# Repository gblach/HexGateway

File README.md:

# HexGateway
An internet gateway for Bluetooth LE, OpenThread and/or Zigbee devices.

It employs three chips:
- nrf52840 - has support for Bluetooth LE, OpenThread and Zigbee networks.
- esp32-c3 - has support for WiFi at 2.4GHz.
- enc28j60 - has support for Ethernet network.

## Hardware
To build your own board you need this [gerber file](HexGateway.zip) and [bill of materials](HexGateway.csv).

Note that U102 is required only if your are using esp32-c3 (U101) without built-in flash memory.

## Programmers
nrf52840 (U1) can be programmed using the standalone [Segger J-Link](https://www.segger.com/products/debug-probes/j-link/) or the on-board Segger J-Link (this can be found for e.g. on [nrf52840dk](https://www.nordicsemi.com/Products/Development-hardware/nRF52840-DK) board). This programmer must be connected to J1 (TagConnect) or J2 (IDC 10) connector.

esp32-c3 (U101) can be programmed using [ESP-Prog](https://docs.espressif.com/projects/espressif-esp-iot-solution/en/latest/hw-reference/ESP-Prog_guide.html). This programmer must be connected to J101 (TagConnect) or J102 (IDC 6) connector.

enc28j60 (U201) does not need to be programmed.

## Software
For the nrf52840 chip you have to write your own software that will meet your requirements. The best way is to use [Zephyr RTOS](https://www.zephyrproject.org/). The board definition for Zephyr can be found in [boards/arm/hexgw1](boards/arm/hexgw1) directory.

esp32-c3 can be controlled with AT commands. To do this, you need to upload [ESP-AT](https://github.com/espressif/esp-at) firmware.

## Sponsorship

The production of these gateways was sponsored by [PCBWay](https://pcbway.com/g/7D2Z6d), they manufacture prototype PCBs and assemble components on the boards. I got 5 almost complete devices from this company for testing and evaluation, I had to solder only connectors for antennas and RJ45 ports by myself.

The visual impression of the boards is very good. All the contacts are gold plated, the silkscreen is readable, the whole board is thoroughly covered with soldiermask and all the components are soldered with a small amount of tin, so I was not worried about a potential short circuit anywhere.

So it remained to upload test programs to check if everything works properly. First I uploaded ESP-AT to the ESP32-C3 chips, and that passed without any problem. Next, I uploaded four programs one at a time to the nRF52840 chips. The first to check if bluetooth works, the second to check WiFi operation, the third to check Ethernet and the fourth to check LEDs. In the case of 4/5 boards, everything works as expected, so they are fully functional devices. However, for the fifth one, the programmer gave me a message that it does not detect the voltage of the processor. With a multimeter I checked the voltage on the VDD pin and there was indeed 0V there. This means that this chip is defective or more likely not all pins are soldered correctly. I am not surprised by this situation, because the nrf52840 chip has very small and densely spaced pins, so if something was to be soldered wrong, it would be with this chip.

My final rating for the quality of devices produced by [PCBWay](https://pcbway.com/g/7D2Z6d) is 4/5 stars, and this is higher than the two competing companies I have worked with. So I will probably change the company where I will produce the PCBs in the future.

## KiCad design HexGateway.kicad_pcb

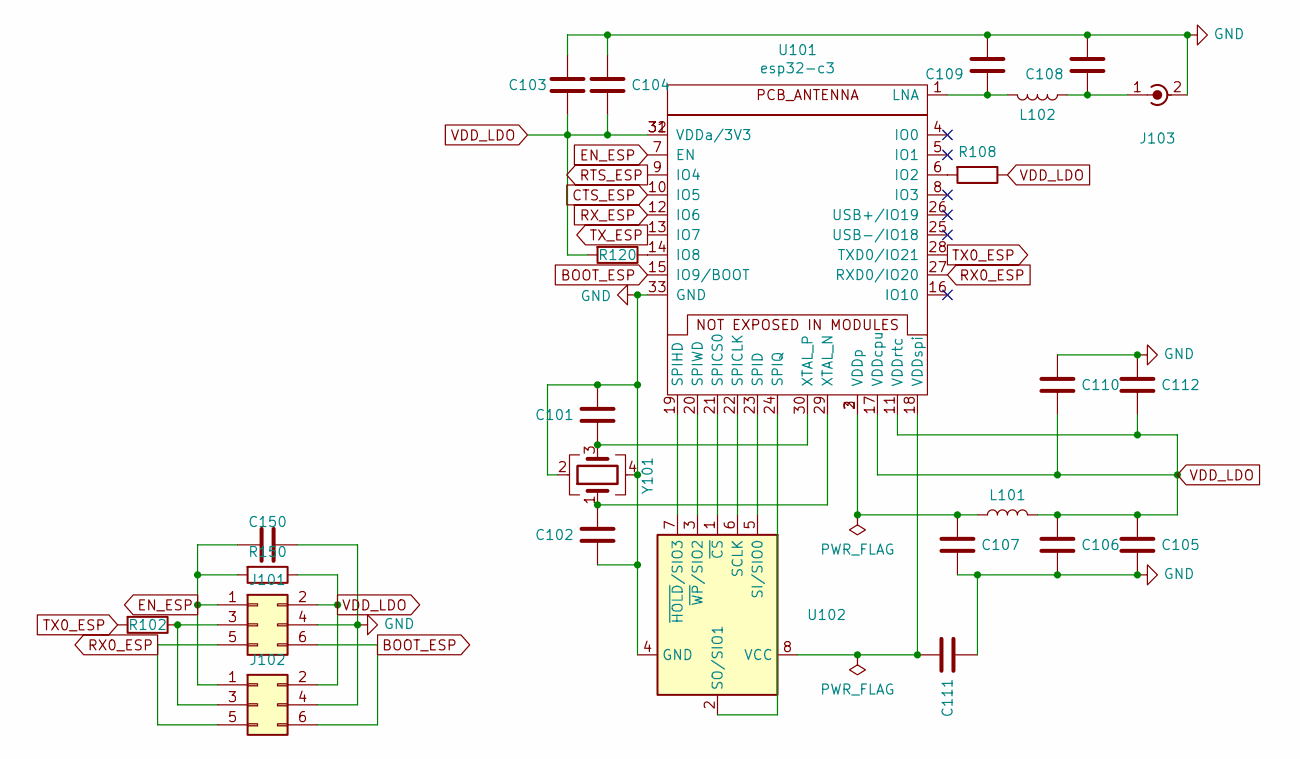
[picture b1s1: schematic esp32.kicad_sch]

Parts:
C101, C102: 20pF; C_0402_1005Metric_Pad0.74x0.62mm_HandSolder; LCSC C1554
C103, C150: 1uF, 20%; C_0402_1005Metric_Pad0.74x0.62mm_HandSolder; LCSC C52923
C104: 10nF, 10%; C_0402_1005Metric_Pad0.74x0.62mm_HandSolder; LCSC C15195
C105: 10uF, 20%; C_0402_1005Metric_Pad0.74x0.62mm_HandSolder; LCSC C15525
C106, C107, C110, C112: 100nF, X7R, 10%; C_0402_1005Metric_Pad0.74x0.62mm_HandSolder; LCSC C1525
C108: 2.0pF; C_0402_1005Metric_Pad0.74x0.62mm_HandSolder; LCSC C1558
C109: 1.5pF; C_0402_1005Metric_Pad0.74x0.62mm_HandSolder; LCSC C23967
C111: 1uF, 20%; C_0402_1005Metric_Pad0.74x0.62mm_HandSolder; LCSC C29266
J101: Conn_02x03_Odd_Even; Tag-Connect_TC2030-IDC-NL_2x03_P1.27mm_Vertical
J102: Conn_02x03_Odd_Even; PinHeader_2x03_P1.27mm_Vertical
J103: Conn_Coaxial; SMA_EdgeMount
L101: 2.0nH, (0.1nH), 450mA; L_0402_1005Metric_Pad0.77x0.64mm_HandSolder; LCSC C87176
L102: 3.9nH; L_0402_1005Metric_Pad0.77x0.64mm_HandSolder; LCSC C14033
R102: 499R, 1%, 1/20W; R_0402_1005Metric_Pad0.72x0.64mm_HandSolder; LCSC C57982
R108, R120, R150: 10k, 1%; R_0402_1005Metric_Pad0.72x0.64mm_HandSolder; LCSC C25744
U101: esp32-c3; QFN-32-1EP_5x5mm_P0.5mm_EP3.7x3.7mm; LCSC C2838500
U102: MX25R3235FM2xx1; SOP-8_5.28x5.23mm_P1.27mm; LCSC C18192
Y101: 40MHz, 15pF, 10ppm; Crystal_SMD_3225-4Pin_3.2x2.5mm; LCSC C90935

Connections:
BOOT_ESP: J101.6, J102.6, U101.15 (IO9/BOOT)
CTS_ESP: U101.10 (IO5); also elsewhere on the board
EN_ESP: C150.1, J101.1, J102.1, R150.2, U101.7 (EN)
GND: C101.2, C102.2, C103.1, C104.1, C105.2, C106.2, C107.2, C108.2, C109.2, C110.1, C111.1, C112.1, C150.2, J101.4, J102.4, J103.2 (Ext), U101.33 (GND), U102.4 (GND), Y101.2, Y101.4; also elsewhere on the board
unnamed: C101.1, U101.30 (XTAL_P), Y101.3
unnamed: C102.1, U101.29 (XTAL_N), Y101.1
unnamed: C107.1, L101.1, U101.2 (VDDp), U101.3 (VDDp)
unnamed: C108.1, J103.1 (In), L102.1
unnamed: C109.1, L102.2, U101.1 (LNA)
unnamed: C111.2, U101.18 (VDDspi), U102.8 (VCC)
unnamed: J101.3, J102.3, R102.1
unnamed: R108.2, U101.6 (IO2)
unnamed: R120.1, U101.14 (IO8)
unnamed: U101.19 (SPIHD), U102.7 (~HOLD/SIO3)
unnamed: U101.20 (SPIWD), U102.3 (~WP/SIO2)
unnamed: U101.21 (SPICS0), U102.1 (~CS)
unnamed: U101.22 (SPICLK), U102.6 (SCLK)
unnamed: U101.23 (SPID), U102.5 (SI/SIO0)
unnamed: U101.24 (SPIQ), U102.2 (SO/SIO1)
RTS_ESP: U101.9 (IO4); also elsewhere on the board
RX0_ESP: J101.5, J102.5, U101.27 (RXD0/IO20)
RX_ESP: U101.12 (IO6); also elsewhere on the board
TX0_ESP: R102.2, U101.28 (TXD0/IO21)
TX_ESP: U101.13 (IO7); also elsewhere on the board
VDD_LDO: C103.2, C104.2, C105.1, C106.1, C110.2, C112.2, J101.2, J102.2, L101.2, R108.1, R120.2, R150.1, U101.11 (VDDrtc), U101.17 (VDDcpu), U101.31 (VDDa/3V3), U101.32 (VDDa/3V3); also elsewhere on the board

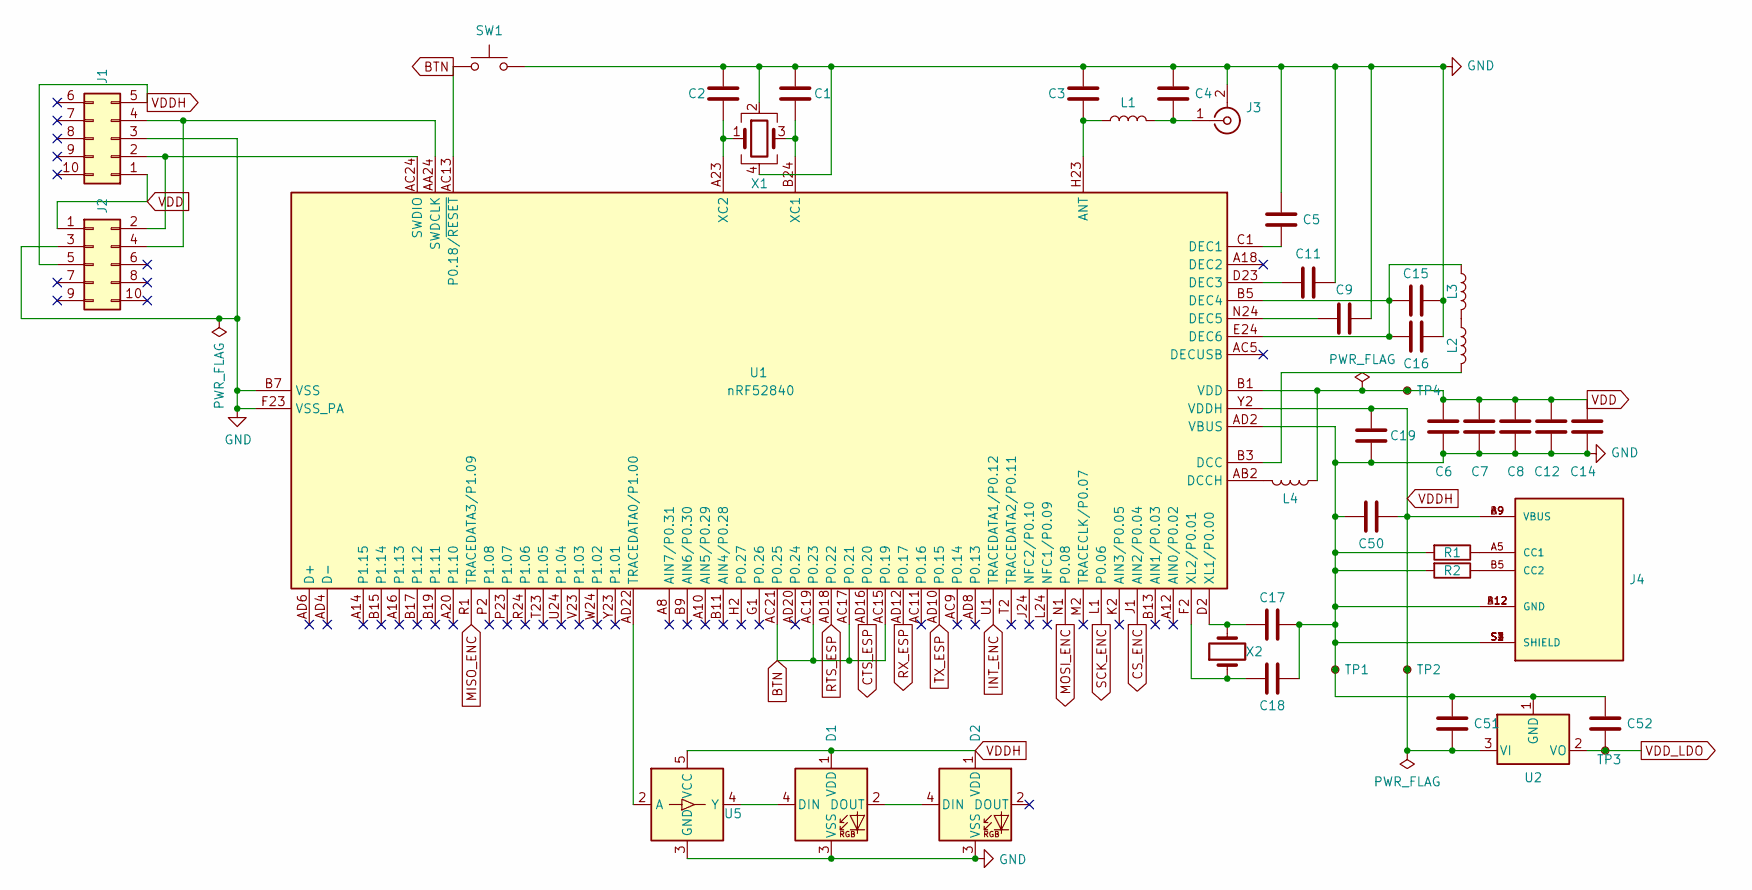
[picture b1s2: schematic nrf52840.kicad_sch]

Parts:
C1, C2, C17, C18: 12pF, NP0, 2%; C_0402_1005Metric_Pad0.74x0.62mm_HandSolder; LCSC C1547
C3: 0.8pF, NP0, 10%; C_0402_1005Metric_Pad0.74x0.62mm_HandSolder; LCSC C326068
C4: 0.5pF, NP0, 10%; C_0402_1005Metric_Pad0.74x0.62mm_HandSolder; LCSC C86284
C5, C7, C8, C12: 100nF, X7R, 10%; C_0402_1005Metric_Pad0.74x0.62mm_HandSolder; LCSC C1525
C6, C19: 4.7uF, X7R, 10%; C_0603_1608Metric_Pad1.08x0.95mm_HandSolder; LCSC C19666
C9: 820pF, NP0, 5%; C_0402_1005Metric_Pad0.74x0.62mm_HandSolder; LCSC C307452
C11: 100pF, NP0, 5%; C_0402_1005Metric_Pad0.74x0.62mm_HandSolder; LCSC C1546
C14, C15: 1.0uF, X7R, 10%; C_0603_1608Metric_Pad1.08x0.95mm_HandSolder; LCSC C15849
C16: 47nF, X7R, 10%; C_0402_1005Metric_Pad0.74x0.62mm_HandSolder; LCSC C26403
C50, C51, C52: 10uF, 20%; C_0402_1005Metric_Pad0.74x0.62mm_HandSolder; LCSC C15525
D1, D2: WS2812B; WS2812B_4020; LCSC C965557
J1: Conn_02x05_Counter_Clockwise; Tag-Connect_TC2050-IDC-NL_2x05_P1.27mm_Vertical_with_bottom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
J2: Conn_02x05_Odd_Even; PinHeader_2x05_P1.27mm_Vertical
J3: Conn_Coaxial; SMA_EdgeMount
J4: USB4125-GF-A_REVA; GCT_USB4125-GF-A_REVA; PARTREV Rev A; LCSC C283540
L1: 4.7nH, 5%; L_0402_1005Metric_Pad0.77x0.64mm_HandSolder; LCSC C13595
L2, L4: 10uH, 80mA, 20%; L_0603_1608Metric_Pad1.05x0.95mm_HandSolder; LCSC C87216
L3: 15nH, 10%; L_0402_1005Metric_Pad0.77x0.64mm_HandSolder; LCSC C27143
R1, R2: 5.1k, 10%; R_0603_1608Metric_Pad0.98x0.95mm_HandSolder; LCSC C23186
SW1: SW_Push; SW_Tactile_SPST_Angled_PTS645Vx31-2LFS
TP1: TestPoint_Small; TestPoint_Pad_1.0x1.0mm
TP2, TP3, TP4: TestPoint_Small; TestPoint_Pad_D1.0mm
U1: nRF52840; Nordic_AQFN-73-1EP_7x7mm_P0.5mm; LCSC C190794
U2: LM1117-3.3; SOT-223-3_TabPin2; LCSC C6186
U5: SN74LV1T34DBV; SOT-23-5_HandSoldering; LCSC C100024
X1: 32MHz, 8pF, 40ppm; Crystal_SMD_2016-4Pin_2.0x1.6mm; LCSC C187794
X2: 32.768kHz, 9pF, 50ppm; Crystal_SMD_3215-2Pin_3.2x1.5mm; LCSC C32346

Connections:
BTN: SW1.2, U1.AC13 (P0.18/~RESET), U1.AC15 (P0.19), U1.AC17 (P0.21), U1.AC19 (P0.23), U1.AC21 (P0.25)
CS_ENC: U1.J1 (AIN2/P0.04); also elsewhere on the board
CTS_ESP: U1.AD16 (P0.20); also elsewhere on the board
GND: C1.1, C2.2, C3.1, C4.1, C5.1, C6.2, C7.2, C8.2, C9.1, C11.1, C12.2, C14.2, C15.1, C16.2, C17.2, C18.1, C19.2, C50.1, C51.1, C52.1, D1.3 (VSS), D2.3 (VSS), J1.3, J2.3, J3.2 (Ext), J4.A12 (GND), J4.B12 (GND), J4.S1 (SHIELD), J4.S2 (SHIELD), J4.S3 (SHIELD), J4.S4 (SHIELD), R1.2, R2.2, SW1.1, TP1.1, U1.AD2 (VBUS), U1.B7 (VSS), U1.EP (VSS), U1.F23 (VSS_PA), U2.1 (GND), U5.3 (GND), X1.2, X1.4; also elsewhere on the board
INT_ENC: U1.U1 (TRACEDATA1/P0.12); also elsewhere on the board
MISO_ENC: U1.R1 (TRACEDATA3/P1.09); also elsewhere on the board
MOSI_ENC: U1.N1 (P0.08); also elsewhere on the board
unnamed: C1.2, U1.B24 (XC1), X1.3
unnamed: C2.1, U1.A23 (XC2), X1.1
unnamed: C3.2, L1.1, U1.H23 (ANT)
unnamed: C4.2, J3.1 (In), L1.2
unnamed: C5.2, U1.C1 (DEC1)
unnamed: C9.2, U1.N24 (DEC5)
unnamed: C11.2, U1.D23 (DEC3)
unnamed: C15.2, C16.1, L3.1, U1.B5 (DEC4), U1.E24 (DEC6)
unnamed: C17.1, U1.D2 (XL1/P0.00), X2.2
unnamed: C18.2, U1.F2 (XL2/P0.01), X2.1
unnamed: D1.2 (DOUT), D2.4 (DIN)
unnamed: D1.4 (DIN), U5.4 (Y)
unnamed: J1.2, J2.2, U1.AC24 (SWDIO)
unnamed: J1.4, J2.4, U1.AA24 (SWDCLK)
unnamed: J4.A5 (CC1), R1.1
unnamed: J4.B5 (CC2), R2.1
unnamed: L2.1, L3.2
unnamed: L2.2, U1.B3 (DCC)
unnamed: L4.2, U1.AB2 (DCCH)
unnamed: U1.AD22 (TRACEDATA0/P1.00), U5.2 (A)
RTS_ESP: U1.AD18 (P0.22); also elsewhere on the board
RX_ESP: U1.AD12 (P0.17); also elsewhere on the board
SCK_ENC: U1.L1 (P0.06); also elsewhere on the board
TX_ESP: U1.AD10 (P0.15); also elsewhere on the board
VDD: C6.1, C7.1, C8.1, C12.1, C14.1, J1.1, J2.1, L4.1, TP4.1, U1.A22 (VDD), U1.AD14 (VDD), U1.AD23 (VDD), U1.B1 (VDD), U1.W1 (VDD); also elsewhere on the board
VDDH: C19.1, C50.2, C51.2, D1.1 (VDD), D2.1 (VDD), J1.5, J2.5, J4.A9 (VBUS), J4.B9 (VBUS), TP2.1, U1.Y2 (VDDH), U2.3 (VI), U5.5 (VCC); also elsewhere on the board
VDD_LDO: C52.2, TP3.1, U2.2 (VO); also elsewhere on the board

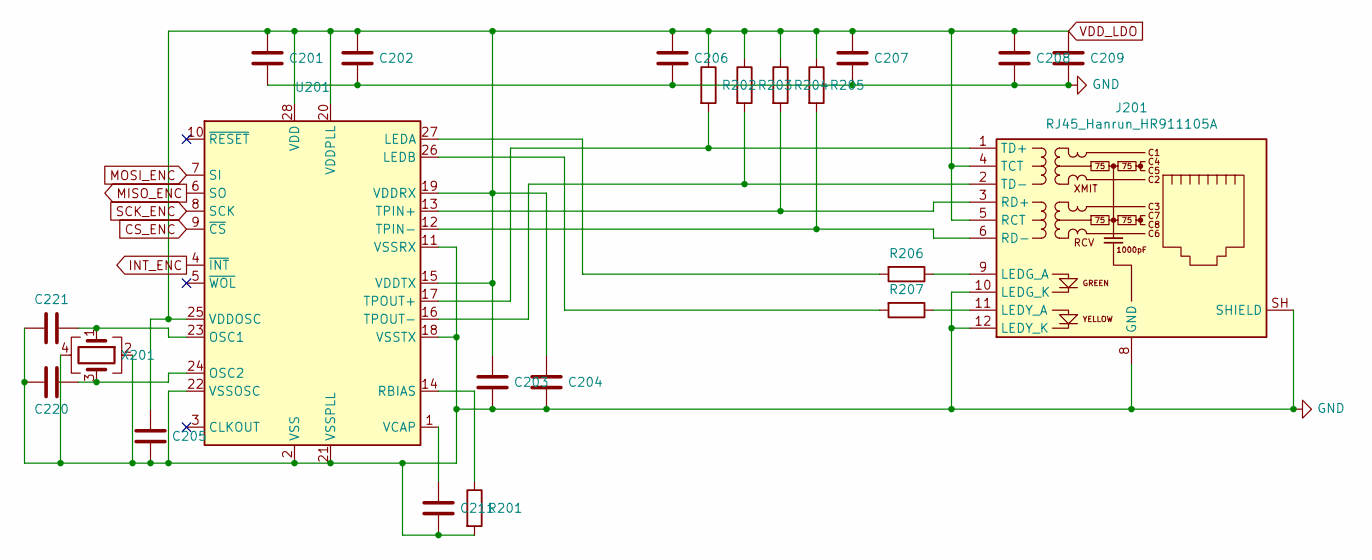
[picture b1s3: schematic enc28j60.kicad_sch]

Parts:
C201, C202, C203, C204, C205, C208, C209: 100nF, X7R, 10%; C_0402_1005Metric_Pad0.74x0.62mm_HandSolder; LCSC C1525
C206, C207: 10nF, 10%; C_0402_1005Metric_Pad0.74x0.62mm_HandSolder; LCSC C15195
C211: 10uF, 20%; C_0402_1005Metric_Pad0.74x0.62mm_HandSolder; LCSC C15525
C220, C221: 20pF; C_0402_1005Metric_Pad0.74x0.62mm_HandSolder; LCSC C1554
J201: RJ45_Hanrun_HR911105A
R201: 2.32k, 1%; R_0402_1005Metric_Pad0.72x0.64mm_HandSolder; LCSC C82297
R202, R203, R204, R205: 50R, 1%; R_0402_1005Metric_Pad0.72x0.64mm_HandSolder; LCSC C25120
R206, R207: 330R; R_0402_1005Metric_Pad0.72x0.64mm_HandSolder; LCSC C25104
U201: ENC28J60x-SS; SSOP-28_5.3x10.2mm_P0.65mm; LCSC C411626
X201: 25MHz, 15/16pF; Crystal_SMD_3225-4Pin_3.2x2.5mm; LCSC C9006

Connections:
CS_ENC: U201.9 (~CS); also elsewhere on the board
GND: C201.2, C202.2, C203.2, C204.2, C205.2, C206.2, C207.2, C208.2, C209.2, C211.2, C220.2, C221.2, J201.8 (GND), J201.10 (LEDG_K), J201.12 (LEDY_K), J201.SH (SHIELD), R201.2, U201.2 (VSS), U201.11 (VSSRX), U201.18 (VSSTX), U201.21 (VSSPLL), U201.22 (VSSOSC), X201.2, X201.4; also elsewhere on the board
INT_ENC: U201.4 (~INT); also elsewhere on the board
MISO_ENC: U201.6 (SO); also elsewhere on the board
MOSI_ENC: U201.7 (SI); also elsewhere on the board
unnamed: C211.1, U201.1 (VCAP)
unnamed: C220.1, U201.24 (OSC2), X201.3
unnamed: C221.1, U201.23 (OSC1), X201.1
unnamed: J201.1 (TD+), R202.2, U201.17 (TPOUT+)
unnamed: J201.2 (TD-), R203.2, U201.16 (TPOUT-)
unnamed: J201.3 (RD+), R204.2, U201.13 (TPIN+)
unnamed: J201.6 (RD-), R205.2, U201.12 (TPIN-)
unnamed: J201.9 (LEDG_A), R206.1
unnamed: J201.11 (LEDY_A), R207.1
unnamed: R201.1, U201.14 (RBIAS)
unnamed: R206.2, U201.27 (LEDA)
unnamed: R207.2, U201.26 (LEDB)
SCK_ENC: U201.8 (SCK); also elsewhere on the board
VDD_LDO: C201.1, C202.1, C203.1, C204.1, C205.1, C206.1, C207.1, C208.1, C209.1, J201.4 (TCT), J201.5 (RCT), R202.1, R203.1, R204.1, R205.1, U201.15 (VDDTX), U201.19 (VDDRX), U201.20 (VDDPLL), U201.25 (VDDOSC), U201.28 (VDD); also elsewhere on the board

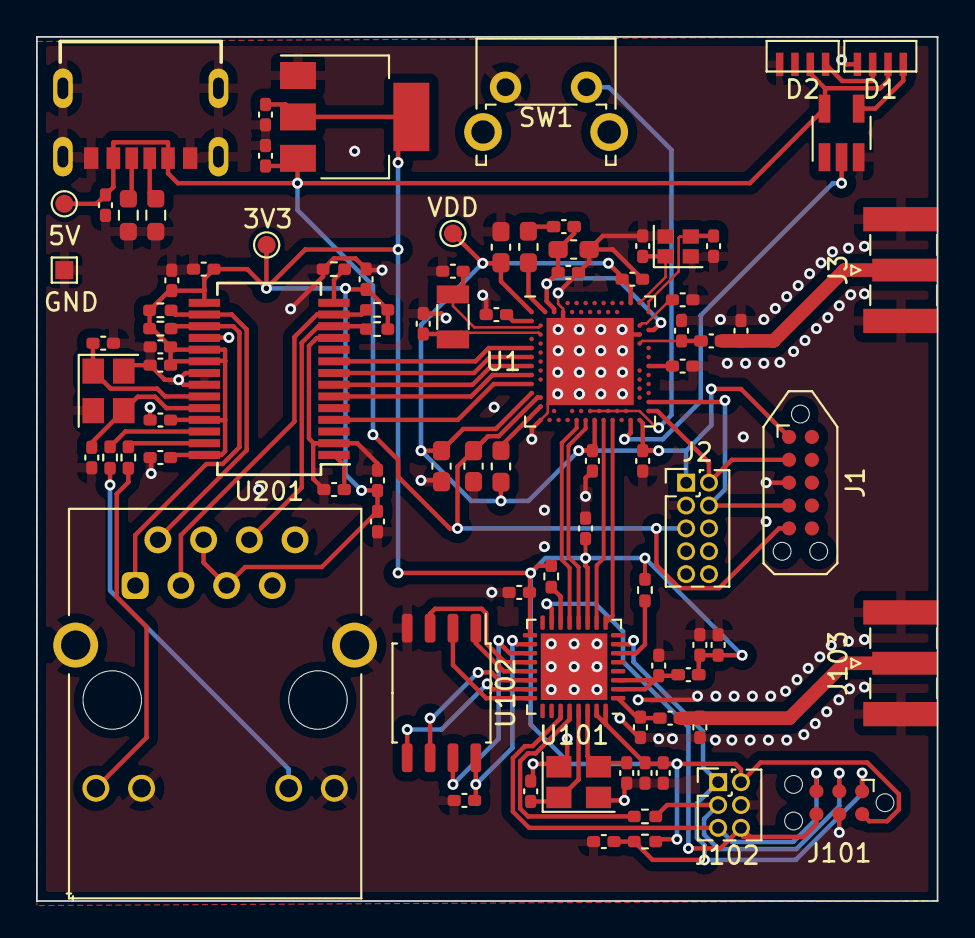
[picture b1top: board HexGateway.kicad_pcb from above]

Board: 2 copper layers, 50.0 x 48.0 mm, 89 parts (0 on the bottom side), 65 nets.

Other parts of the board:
3V3, 5V: TestPoint_Small; TestPoint_Pad_D1.0mm
GND: TestPoint_Small; TestPoint_Pad_1.0x1.0mm
VDD: TestPoint_Small; TestPoint_Pad_D1.0mm

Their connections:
GND: GND.1; also elsewhere on the board
VDD: VDD.1; also elsewhere on the board
VDDH: 5V.1; also elsewhere on the board
VDD_LDO: 3V3.1; also elsewhere on the board

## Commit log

2022-01-15 Initial import
2022-10-23 Remove header
2022-11-09 Add .gitignore
2022-11-30 Add support for pinctrl
2023-01-28 Remove deprecated labels
2023-01-28 Prepend init.h with zephyr/ in #include statement
2023-01-28 Add support for pyOCD, OpenOCD and Black Magic Probe
2023-02-20 Add sponsorship info
2024-01-27 Update project to KiCad 7
